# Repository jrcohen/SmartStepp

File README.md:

# SmartStepp

### Combination Driver and Encoder for Nema 17 stepper motors
Features:

 * Compact design mounts on the back of the motor
 * Chainable connections (12V Power, Logic Power, SPI) - Hook up multiple motors in series connected to just one microcontroller
 * Compatible with A4988 and DRV8825 stepper motor drivers
 * 14-bit magnetic encoder (AS5047d)
 * Encoder only version is RAMPS 1.4 compatible 

The aim of this project is to create inexpensive Nema 17 and Nema 23 motor encoders/drivers. These boards allow for plug-and-play stepper motor control with extremely precise position readouts once fully calibrated. 

Useful for 3D printers to provide higher precision movement and dynamic error correction for any missed steps (like if the printer gets bumped or stops mid-print).
Other potential applications include robotics/robot arms, process automation machines, hobby CNC machines, any other application needing precise repeatability under different loads.

Project hardware variants:

 * Motor driver only - target cost under $10
 * Encoder only - target cost under $15
 * Driver/Encoder combo - target cost under $20

Future Software compatibility:

 * Arduino Library
 * Python Library (for standalone raspberry pi use)
 * Marlin 
 * GRBL

This project draws inspiration from [Mechaduino](https://github.com/jcchurch13/Mechaduino-Firmware/blob/master/README.md), but hopefully will have its own niche applications

Released under the Creative Commons Attribution Share-Alike 4.0 License

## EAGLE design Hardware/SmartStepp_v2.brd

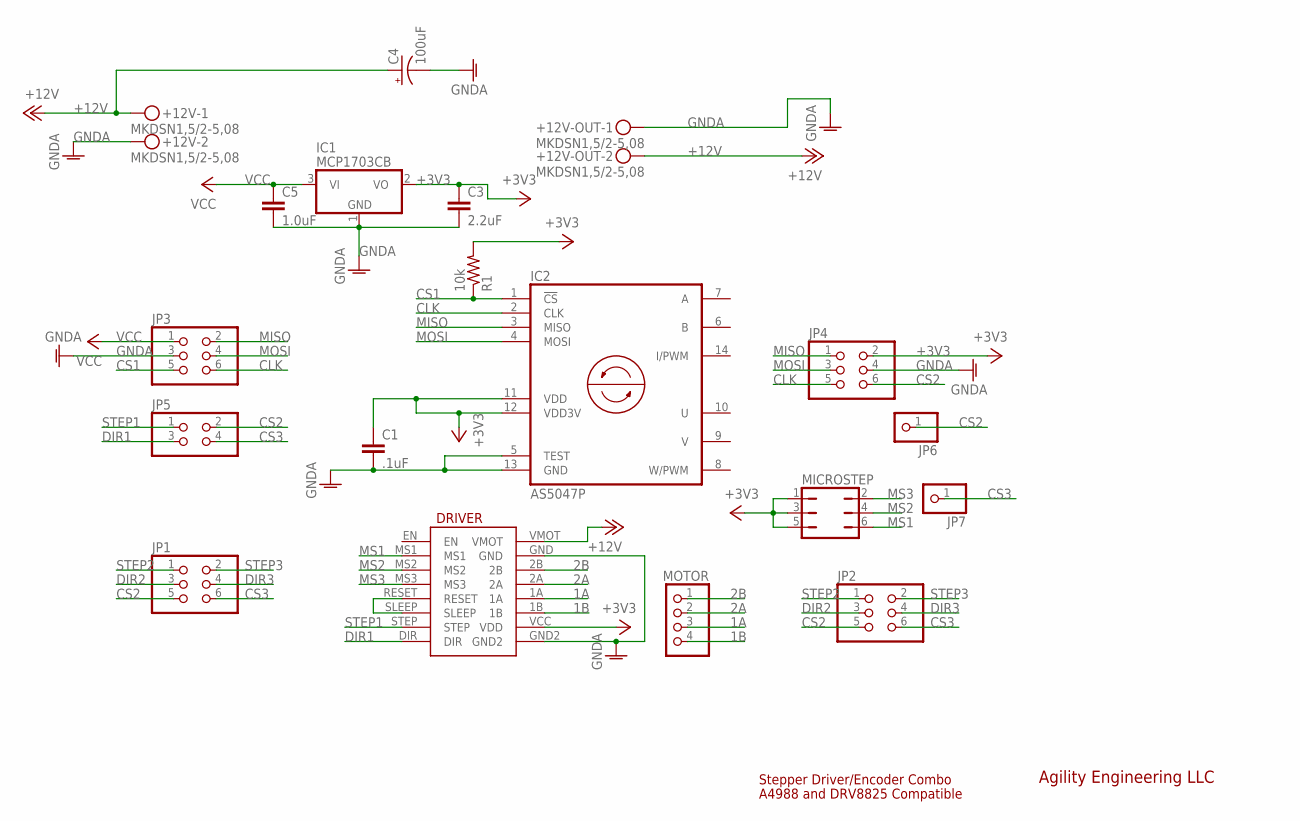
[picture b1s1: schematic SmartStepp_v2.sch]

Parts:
+12V, +12V-OUT: MKDSN1,5/2-5,08
C1: .1uF; C0805
C3: 2.2uF; C0805
C4: 100uF; 153CLV-0605
C5: 1.0uF; C0805
DRIVER: A4988; MOTOR_DRIVER
IC1: MCP1703CB; SOT23
IC2: AS5047P; TSSOP14
JP1, JP2, JP3, JP4: PINHD-2X3; 2X03
JP5: PINHD-2X2; 2X02
JP6, JP7: PINHD-1X1; 1X01
MICROSTEP: JP3Q
MOTOR: PINHD-1X4; 1X04
R1: 10k; R0805

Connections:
1A: DRIVER.1A, MOTOR.3
1B: DRIVER.1B, MOTOR.4
2A: DRIVER.2A, MOTOR.2
2B: DRIVER.2B, MOTOR.1
+3V3: C1.1, C3.1, DRIVER.VCC (VDD), IC1.2 (VO), IC2.11 (VDD), IC2.12 (VDD3V), JP4.2, MICROSTEP.1, MICROSTEP.3, MICROSTEP.5, R1.2
+12V: +12V.1, +12V-OUT.2, C4.+, DRIVER.VMOT
CLK: IC2.2 (CLK), JP3.6, JP4.5
CS1: IC2.1 (!CS!), JP3.5, R1.1
CS2: JP1.5, JP2.5, JP4.6, JP5.2, JP6.1
CS3: JP1.6, JP2.6, JP5.4, JP7.1
DIR1: DRIVER.DIR, JP5.3
DIR2: JP1.3, JP2.3
DIR3: JP1.4, JP2.4
GNDA: +12V.2, +12V-OUT.1, C1.2, C3.2, C4.-, C5.2, DRIVER.GND, DRIVER.GND2, IC1.1 (GND), IC2.5 (TEST), IC2.13 (GND), JP3.3, JP4.4
MISO: IC2.3 (MISO), JP3.2, JP4.1
MOSI: IC2.4 (MOSI), JP3.4, JP4.3
MS1: DRIVER.MS1, MICROSTEP.6
MS2: DRIVER.MS2, MICROSTEP.4
MS3: DRIVER.MS3, MICROSTEP.2
unnamed: DRIVER.RESET, DRIVER.SLEEP
STEP1: DRIVER.STEP, JP5.1
STEP2: JP1.1, JP2.1
STEP3: JP1.2, JP2.2
VCC: C5.1, IC1.3 (VI), JP3.1

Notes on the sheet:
Stepper Driver/Encoder Combo
A4988 and DRV8825 Compatible
Agility Engineering LLC

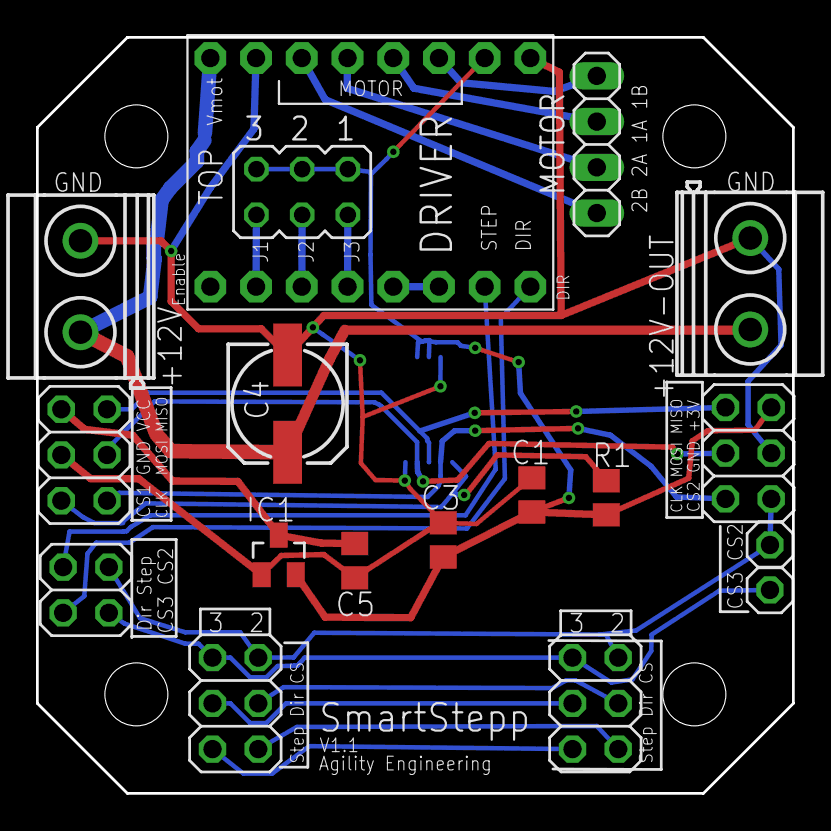
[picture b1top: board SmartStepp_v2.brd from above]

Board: 2 copper layers, 42.0 x 42.0 mm, 19 parts (1 on the bottom side), 24 nets.

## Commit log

2017-06-22 Update README.md
    capitalized name
2017-06-22 Create LICENSE.md
    open source license
2017-06-22 Rename TableData.cpp to Smartstep/TableData.cpp
    Put file in folder
2017-06-22 Rename TableData.h to Smartstep/TableData.h
    Put file in folder
2017-06-22 Rename motorlib.h to Smartstep/motorlib.h
    Put file in folder
2017-06-22 Rename motortab.cpp to Smartstep/motortab.cpp
    Put file in folder
2017-06-22 Rename motortest.ino.ino to Smartstep/motortest.ino
    Put file in folder and deleted duplicate .ino in filename
2017-06-27 New ReadMe file uploaded
2017-06-28 photo upload for description
2017-07-07 Images of schematic and board files for StartStepp v1
2017-07-07 Board and schematic eagle files
2017-07-07 testing the repo in Atom
2017-07-07 just the hi
2017-07-07 master test
2017-07-07 test stage
2017-07-07 master
2017-07-07 mm test
2017-08-02 Correct image file name to match "V2" notation
2017-08-02 Uploaded correctly named BRD and SCH images

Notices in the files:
parts and their libraries:
ams: Copyright (C) 2015, Bob Starr
